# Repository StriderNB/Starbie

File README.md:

# Starbie

Week 1 project of Half Life event hosted by Hack Club. The starter project Starbie with an additional feature, light sensing.
# Details
Simmilar to the starter project Starbie which has two buttons to control it and a character that can nap, heart, jump, or run.

I added an additional photoresistor which at the moment only allows Starbie to sleep when it gets to a certain threshold of darkness. 

# Controls
The left button opens the radial menu, it's second press choses the highlighted action.

The right button shows/hides the stats screen.

The radial menu is controlled by tilting the Starbie in the direction of a desired action.

# BOM
| Item | Qty | Supplier | Cost/item | Total Cost | Link |
| :--- | :---: | :--- | :---: | :---: | :--- |
| Conn_01x08_Pin & Conn_01x04_Pin | 1 | Aliexpress | $2.12 | $2.12 | [Link](https://aliexpress.us) |
| 10k Resistor | 50 | AliExpress | $0.03 | $1.50 | [Link](https://aliexpress.us) |
| GL5528 Photoresistor | 10 | AliExpress | $0.25 | $2.50 | [Link](https://aliexpress.us) |
| SW_Push | 10 | AliExpress | $0.20 | $2.00 | [Link](https://aliexpress.us) |
| ESP32-C3 | 1 | AliExpress | $7.02 | $7.02 | [Link](https://aliexpress.us) |
| DHT11 | 1 | AliExpress | $1.46 | $1.46 | [Link](https://aliexpress.us) |
| PCB | 1 | PCBWay | $5.00 | $5.00 | [Link](https://pcbway.com) |
| MPU 6050 | 1 | AliExpress | $2.19 | $2.19 | [Link](https://aliexpress.us) |
| Keycaps | 10 | AliExpress | $0.30 | $3.00 | [Link](https://aliexpress.us) |
| Estimated total shipping | 1 | | | $8.30 | |

# Additional images

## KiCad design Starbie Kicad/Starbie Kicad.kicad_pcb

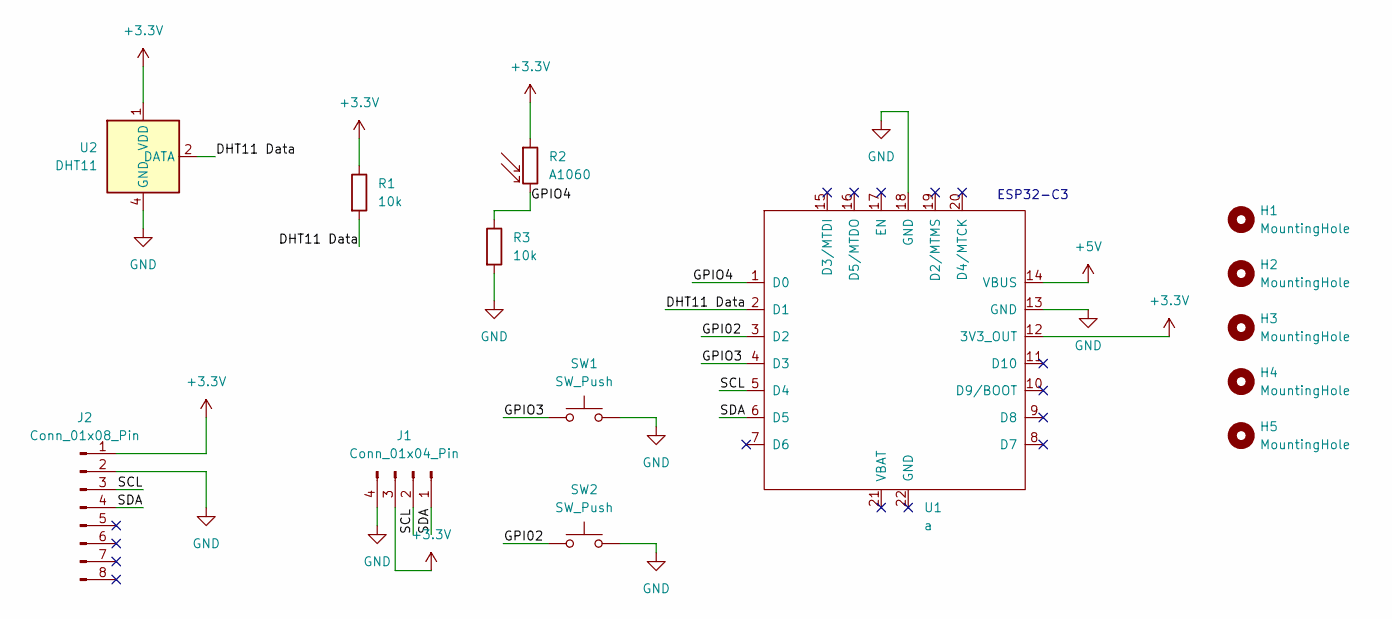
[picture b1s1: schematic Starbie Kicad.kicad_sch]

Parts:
H1, H2, H3, H4, H5: MountingHole; MountingHole_2.2mm_M2
J1: Conn_01x04_Pin; Display_128x64_096_I2C
J2: Conn_01x08_Pin; PinHeader_1x08_P2.54mm_Vertical
R1, R3: 10k; R_Axial_DIN0204_L3.6mm_D1.6mm_P7.62mm_Horizontal
R2: A1060; R_LDR_D6.4mm_P3.4mm_Vertical
SW1, SW2: SW_Push; SW_Cherry_MX_1.00u_PCB
U1: a; XIAO-ESP32-C3-SMD
U2: DHT11; Aosong_DHT11_5.5x12.0_P2.54mm

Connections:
+3.3V: J1.3, J2.1, R1.1, R2.1, U1.12 (3V3_OUT), U2.1 (VDD)
+5V: U1.14 (VBUS)
/DHT11 Data: R1.2, U1.2 (D1), U2.2 (DATA)
/GPI02: SW2.1, U1.3 (D2)
/GPIO3: SW1.1, U1.4 (D3)
/GPIO4: R2.2, R3.1, U1.1 (D0)
/SCL: J1.2, J2.3, U1.5 (D4)
/SDA: J1.1, J2.4, U1.6 (D5)
GND: J1.4, J2.2, R3.2, SW1.2, SW2.2, U1.13 (GND), U1.18 (GND), U2.4 (GND)

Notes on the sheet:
ESP32-C3

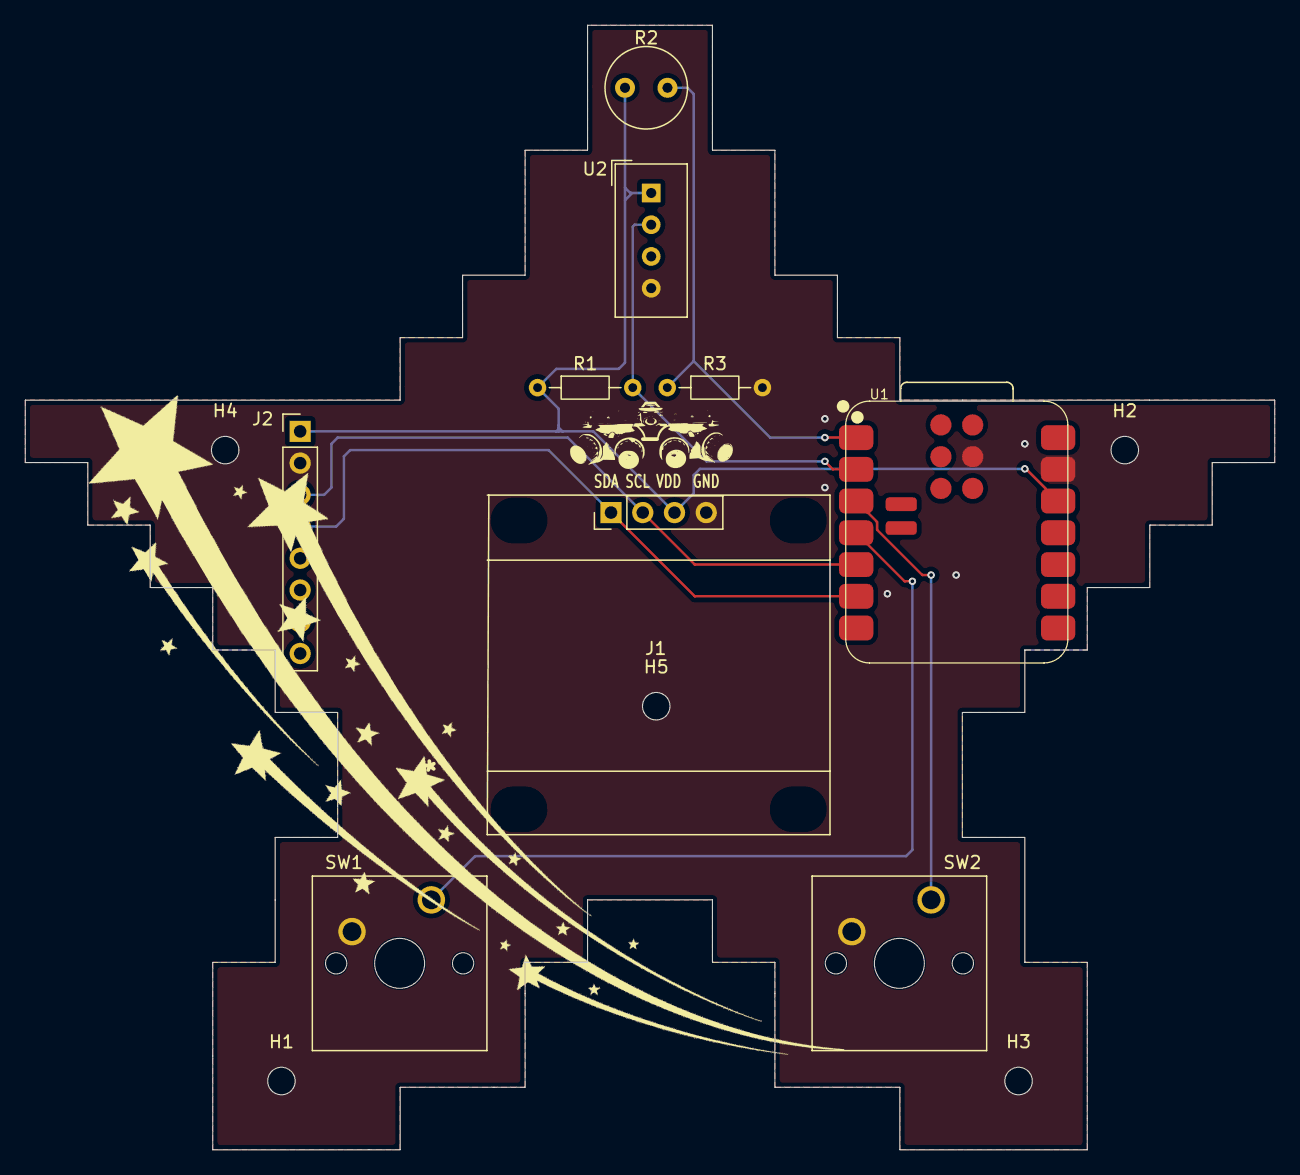
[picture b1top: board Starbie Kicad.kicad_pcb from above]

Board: 2 copper layers, 100.0 x 90.0 mm, 16 parts (0 on the bottom side), 8 nets.

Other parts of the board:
*: LOGO
-: LOGO

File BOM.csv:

Item,Qty,Supplier,Cost/item,Total Cost,link
Conn_01x04_Pin,1,,$0.00,$0.00,
Conn_01x08_Pin,1,,$0.00,$0.00,
10k,2,,$0.00,$0.00,
A1060,1,,$0.00,$0.00,
SW_Push,2,,$0.00,$0.00,
a,1,,$0.00,$0.00,
DHT11,1,,$0.00,$0.00,
Estimated total shipping,1,,,$0.00,
